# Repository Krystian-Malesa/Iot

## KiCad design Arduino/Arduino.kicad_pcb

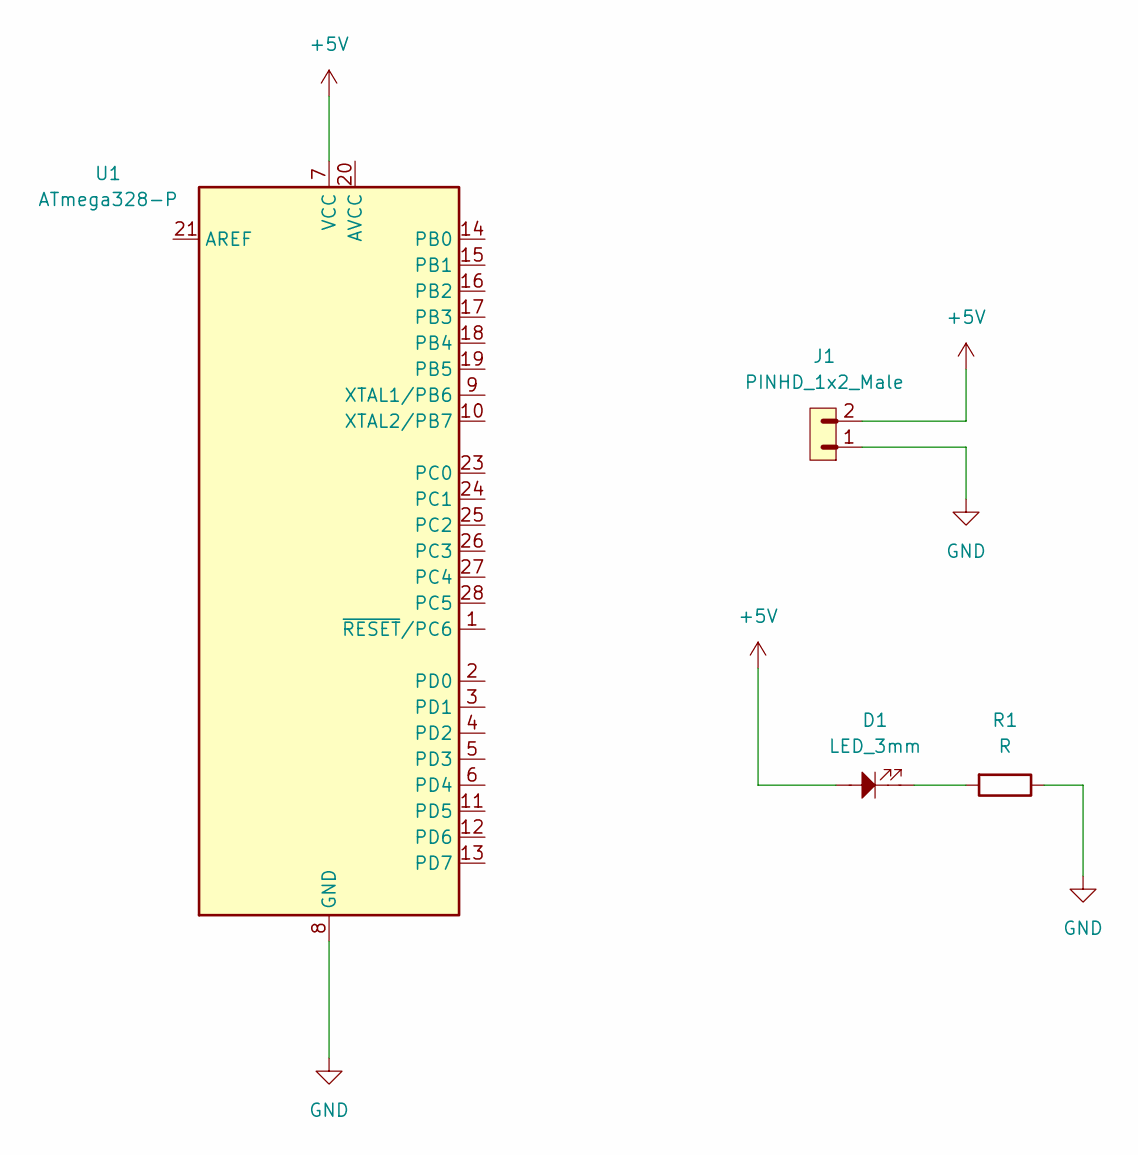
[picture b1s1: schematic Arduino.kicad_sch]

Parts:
D1: LED_3mm; LED_D3.0mm
J1: PINHD_1x2_Male; PinHeader_1x02_P2.54mm_Vertical
R1: R; R_Axial_DIN0207_L6.3mm_D2.5mm_P7.62mm_Horizontal
U1: ATmega328-P; DIP-28_W7.62mm

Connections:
+5V: D1.2, J1.2, U1.7 (VCC)
GND: J1.1, R1.1, U1.8 (GND), U1.22 (GND)
unnamed: D1.1, R1.2

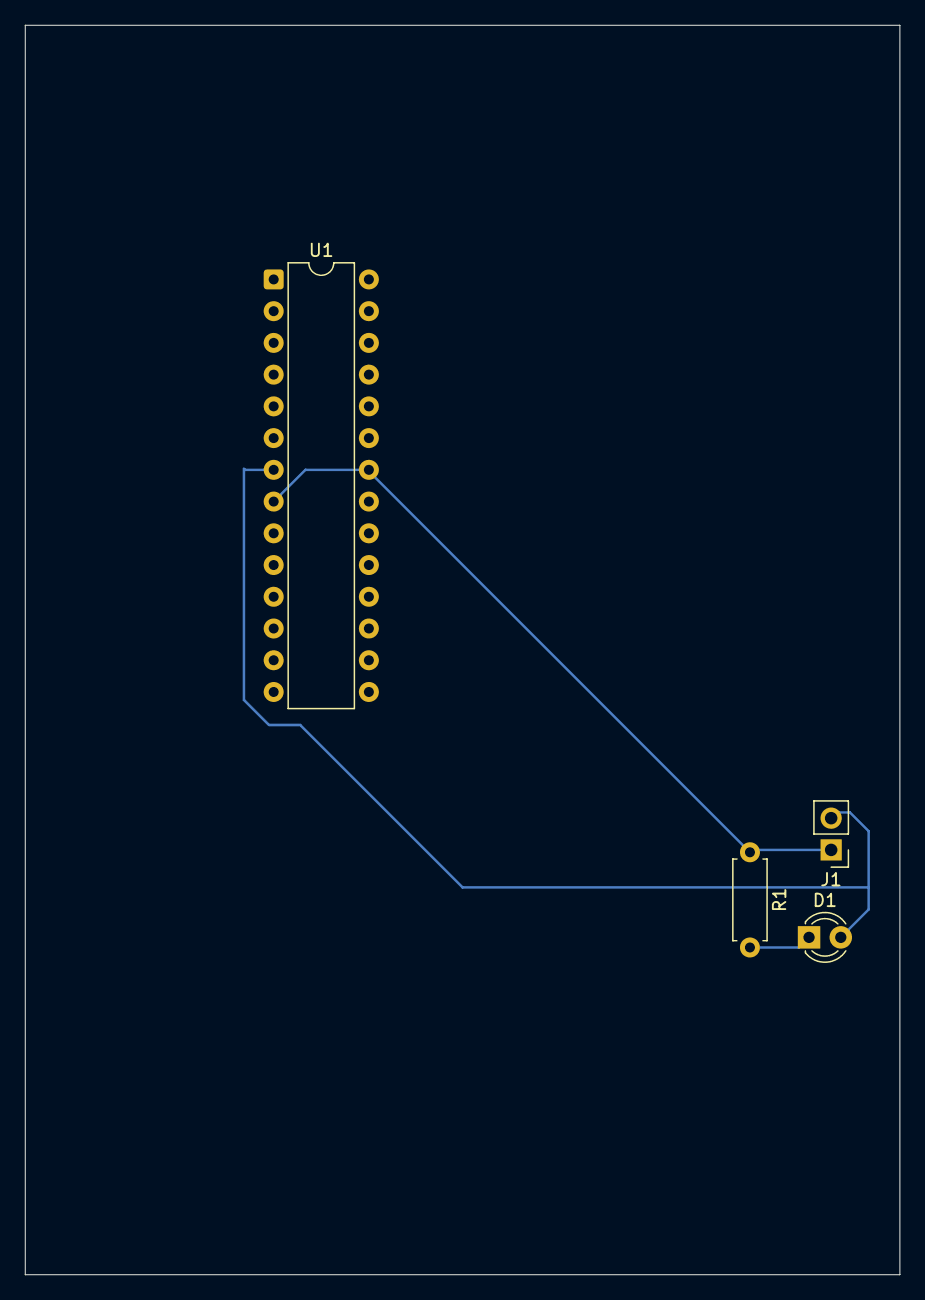
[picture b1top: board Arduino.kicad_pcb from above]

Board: 2 copper layers, 70.0 x 100.0 mm, 4 parts (0 on the bottom side), 3 nets.

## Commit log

2025-11-03 Version 0.0.1
